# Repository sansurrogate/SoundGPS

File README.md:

# SoundGPS
音による測位システム

## ハードウェア

## デモ

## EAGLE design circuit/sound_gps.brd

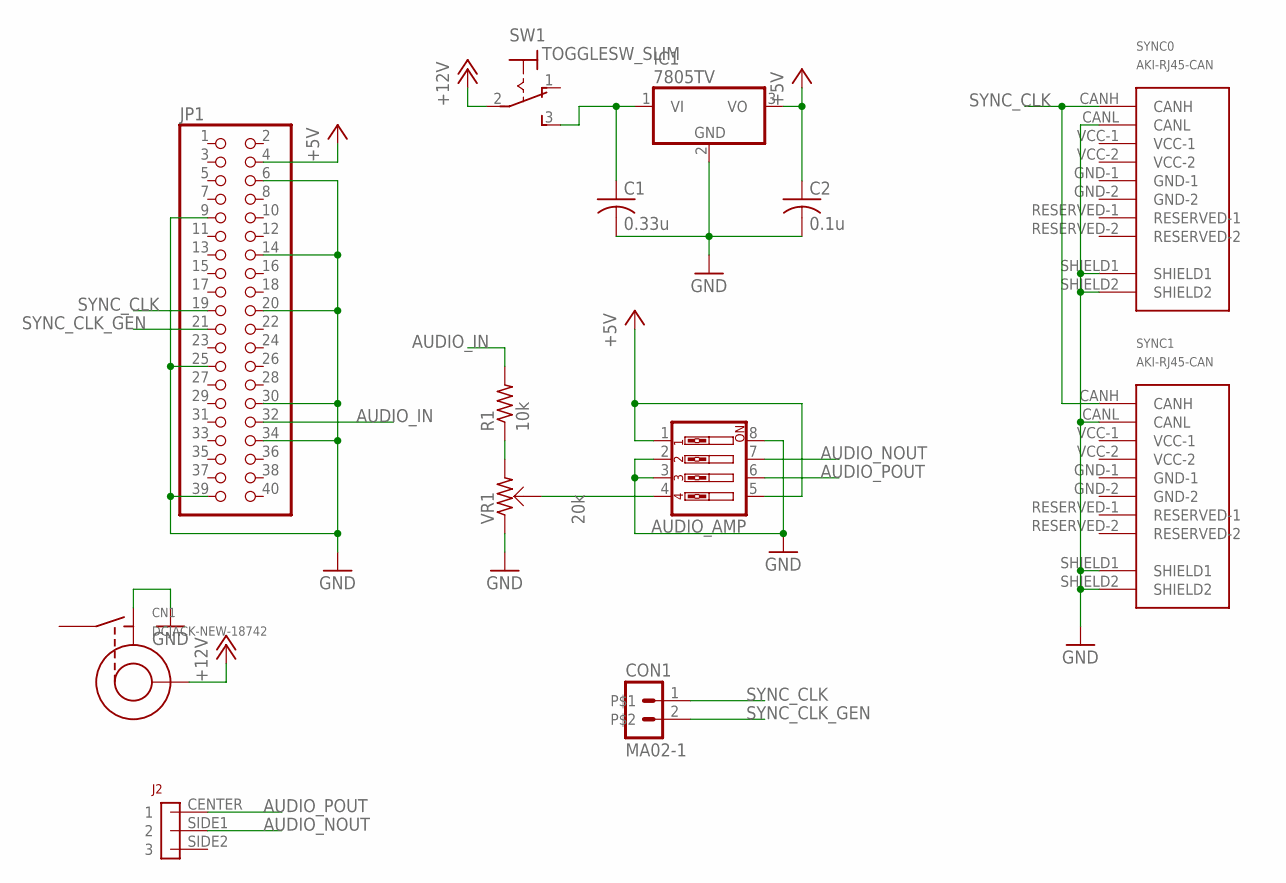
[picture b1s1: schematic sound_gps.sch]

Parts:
AUDIO_AMP: SW_DIP-4; EDG-04
C1: 0.33u; 2012-C
C2: 0.1u; 2012-C
CN1: DCJACK-NEW-18742; 18742
CON1: MA02-1
IC1: 7805TV; TO220V
J2: DCJACK
JP1: PINHD-2X20; 2X20
R1: 10k; 1608
SW1: TOGGLESW_SLIM
SYNC0, SYNC1: AKI-RJ45-CAN
VR1: 20k; VR-637A

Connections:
+5V: AUDIO_AMP.1, AUDIO_AMP.5, C2.1, IC1.3 (VO), JP1.4
+12V: CN1.P$1 (CENTER), SW1.2
AUDIO_IN: JP1.32, R1.2
AUDIO_NOUT: AUDIO_AMP.7, J2.SIDE1 (2)
AUDIO_POUT: AUDIO_AMP.6, J2.CENTER (1)
GND: AUDIO_AMP.2, AUDIO_AMP.3, AUDIO_AMP.8, C1.2, C2.2, CN1.P$2 (TIP), IC1.2 (GND), JP1.6, JP1.9, JP1.14, JP1.20, JP1.25, JP1.30, JP1.34, JP1.39, SYNC0.CANL, SYNC0.SHIELD1, SYNC0.SHIELD2, SYNC1.CANL, SYNC1.SHIELD1, SYNC1.SHIELD2, VR1.1
GND-1: SYNC0.GND-1, SYNC1.GND-1
GND-2: SYNC0.GND-2, SYNC1.GND-2
unnamed: AUDIO_AMP.4, VR1.BR
unnamed: R1.1, VR1.2
unnamed: C1.1, IC1.1 (VI), SW1.3 (S)
SYNC_CLK: CON1.1, JP1.19, SYNC0.CANH, SYNC1.CANH
SYNC_CLK_GEN: CON1.2, JP1.21
VCC-1: SYNC0.VCC-1, SYNC1.VCC-1
VCC-2: SYNC0.VCC-2, SYNC1.VCC-2

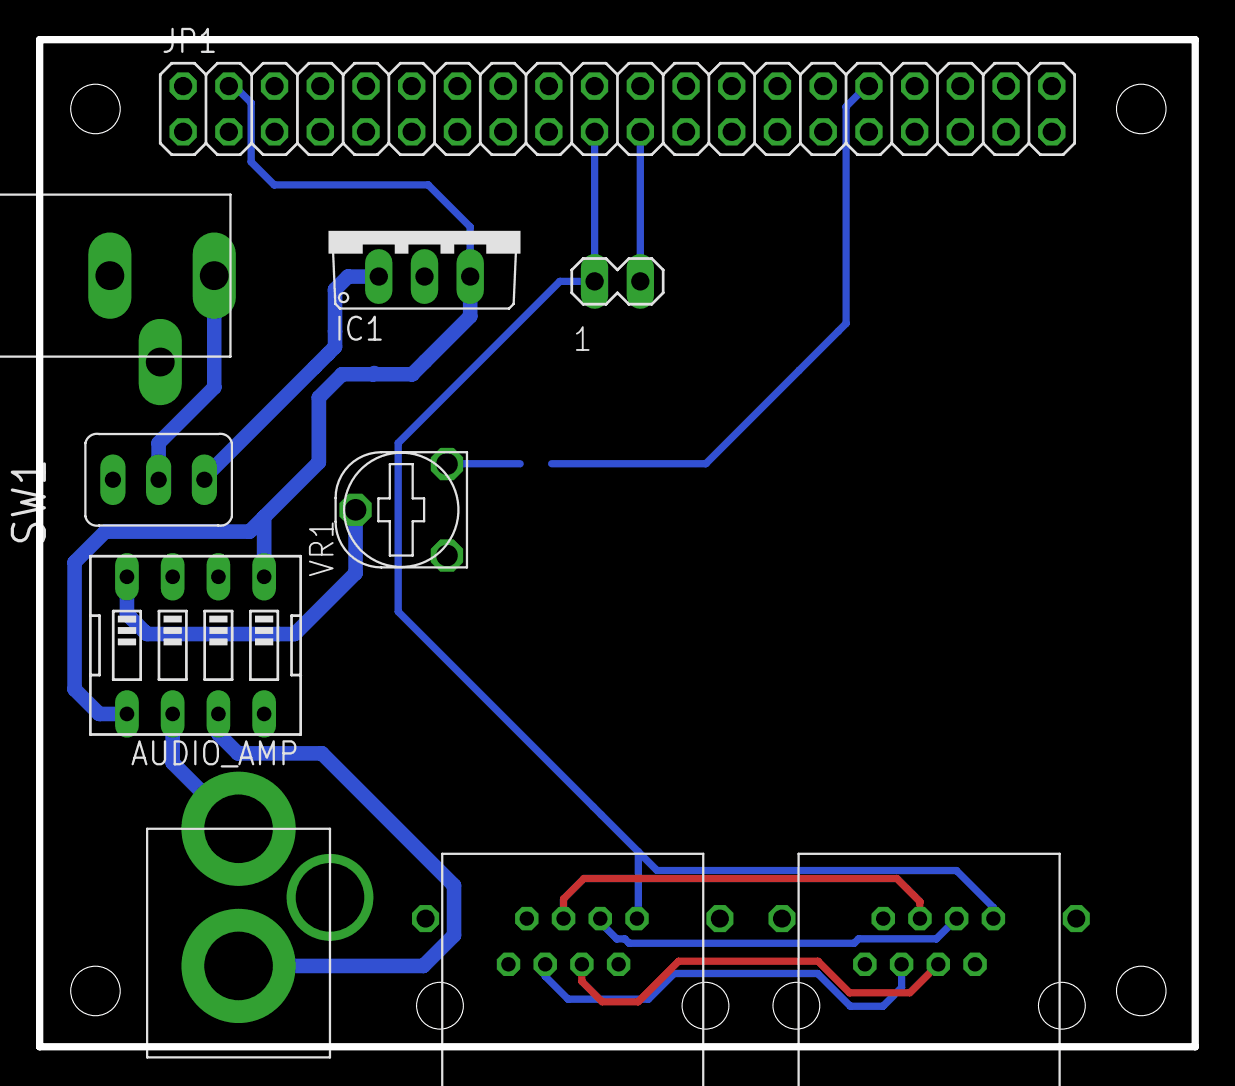
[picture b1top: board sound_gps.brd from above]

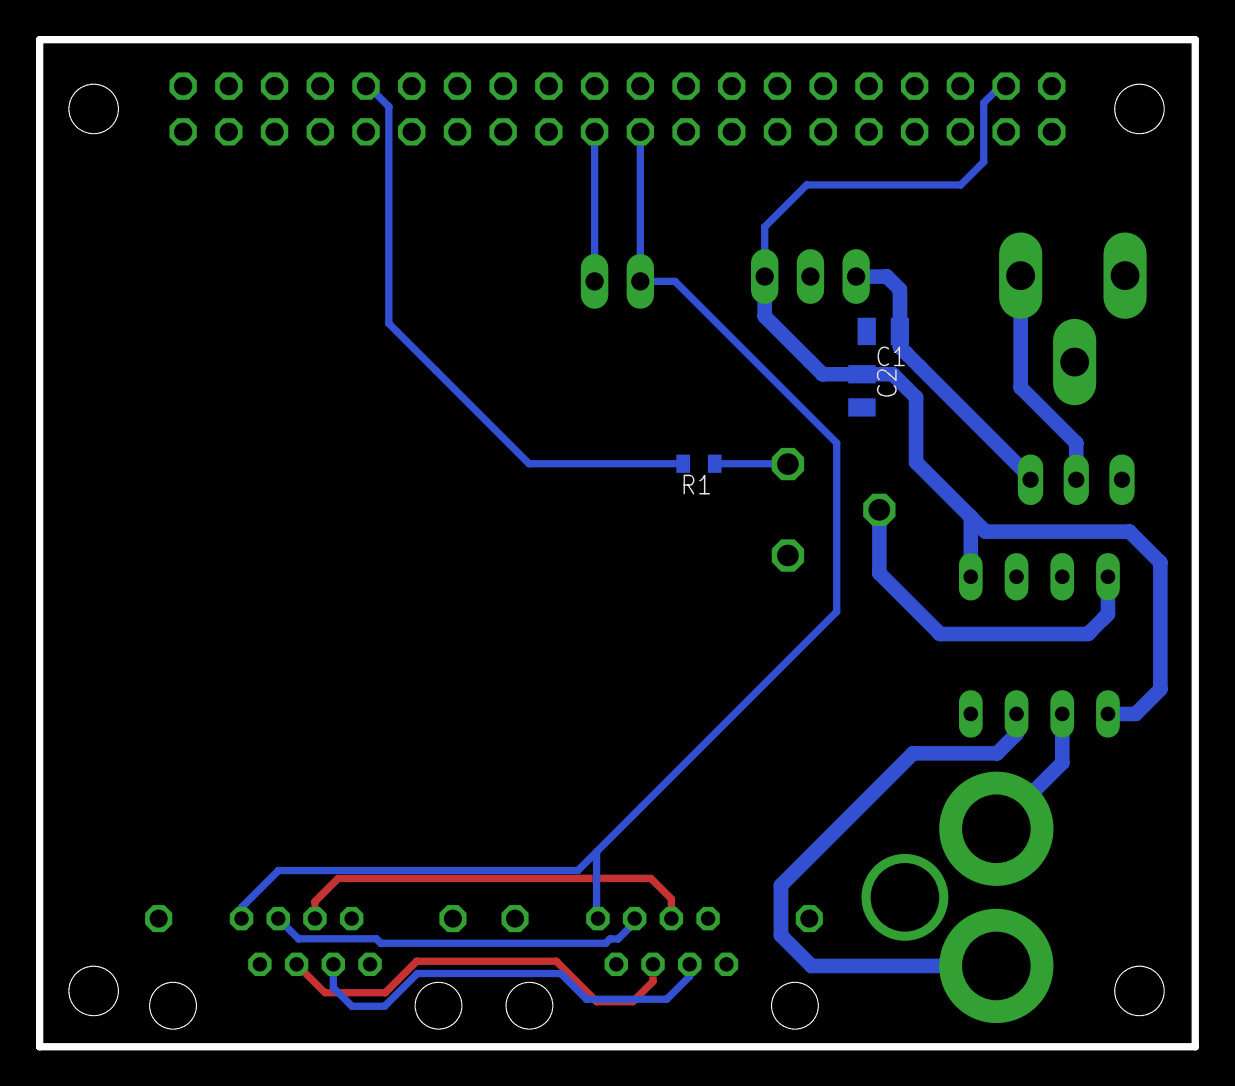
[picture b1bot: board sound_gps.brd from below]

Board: 2 copper layers, 64.2 x 56.0 mm, 13 parts (3 on the bottom side), 15 nets.

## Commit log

2016-12-06 とりあえずgpioとuartを動くようにした
2016-12-07 割り込みを動くようにした (ARMのハイパーバイザモードという闇)
2016-12-07 ディレクトリの整理
2016-12-07 関数名を統一した
2016-12-07 コメントを書いた
2016-12-09 pwmを実装し、矩形波が出力できることを確認した
2016-12-10 rawデータをfftして表示したい。のだけど、まだ区間の選定とかどうやって描画するのかとかを決めてない
2016-12-11 rpi2以前のボードに対応した
2016-12-11 ディレクトリ構造を変えた
2016-12-12 gpio割り込みを実装途中(リファクタリングまだ)
2016-12-13 pwmの非推奨な命令を正した
2016-12-13 hello world用のブランチ
2016-12-13 gpioの割り込み周りを整理した
2016-12-13 make時にdumpfileを作成するようにした
2016-12-14 raw2freqというfftする奴を作った
2016-12-15 .gitignoreの修正
2016-12-15 ファイルの整理
2016-12-15 ディレクトリ名、researchをreserchと間違えてた...幼稚園からやり直してきます...
2016-12-16 sin波のfftとか，logをrawデータ化するプログラムとか作った
2016-12-16 pskのrawデータ発生プログラムを作成した
2016-12-16 gitignoreを変更してバックアップファイルやバイナリをignoreするようにした
2016-12-17 .gitignoreで実行ファイルをignoreするようにした。
2016-12-17 psk send.cでshort型をint16_tに修正した
2016-12-17 cdmaをプロットした
2016-12-17 特定の周波数だけ取り出すプログラムを作った 使い方 ./raw2one_freq.exe [窓幅] [サンプリングレート] [みたい周波数] < rawデータ > logファイル
    の後に
    gnuplot
    plot "logデータ" u 0:6 w l
    とか（5が長さ，6が角度になります）
2016-12-19 同期用のプログラムを書いた
2016-12-21 goldから相互相関をとったやつを出力するプログラムを書いた
2016-12-21 add test data
2016-12-21 同期システム(仮)
2016-12-21 add cdma2
2016-12-21 add cdma3
2016-12-29 research/psk/multi_channel/ 内にゴールド系列を選択して個別に鳴らせるようなプログラムを作った(テスト用)
2016-12-30 2つのPCからGold系列を鳴らして録音した
2016-12-30 LICENSEを修正した
2016-12-30 ゴールド系列からデータを取り出すプログラムを書いた
2016-12-30 ちょっとした修正
2016-12-30 far_ch0もデータ取った
2016-12-30 far_ch0をサンプリングした
2017-01-04 音の減衰データをとった
2017-01-05 pwmをdmaで駆動できるように実装した
2017-01-05 dmaを用いたpwmを同期し，ズレが20us以内に収まることを確認した．
2017-01-05 音の減衰を定量化した
2017-01-05 さっきの音の距離減衰のグラフは実は間違いで，こっちが正しいと思われる
2017-01-06 実際のスピーカーで拡散符号を試してみた
2017-01-06 gold符号を鳴らせた
2017-01-07 回路を設計した(circuit-1.0)
2017-01-07 スイッチを追加した
2017-01-08 circuit version 2.0
2017-01-09 circuit version 3.0
2017-01-10 実機でデータをとった
2017-01-10 sicを試したが，ダメっ
2017-01-10 チャネル数を4本に増やした
2017-01-10 beta版もいくつかdataとってみた
2017-01-12 127bitのゴールド系列を試した
2017-01-12 127bitのgold codeを試してみた
2017-01-12 分析用のスクリプトを書いた
2017-01-12 スピーカーから遠くと近くでデータをとってみたが，やはり1chだけだと大丈夫っぽい
2017-01-12 __pycache__フォルダをignoreするようにした
2017-01-13 系列生成用のプログラムを書いた
2017-01-13 1023bitの嵩系列により，動作してるっぽいことを確認した
2017-01-13 1023bitの嵩系列で取ったデータ達
2017-01-13 ディレクトリ構造の変更とケースの底面を作成した
2017-01-13 ケースの天面と底面を設計した
2017-01-14 底面にch番号を書いた
2017-01-16 動いた!!!
2017-01-16 発表の資料作りのために少し変更を加えた
2017-01-16 READMEを変更
2017-01-28 added demo movie
2018-05-25 modified README
